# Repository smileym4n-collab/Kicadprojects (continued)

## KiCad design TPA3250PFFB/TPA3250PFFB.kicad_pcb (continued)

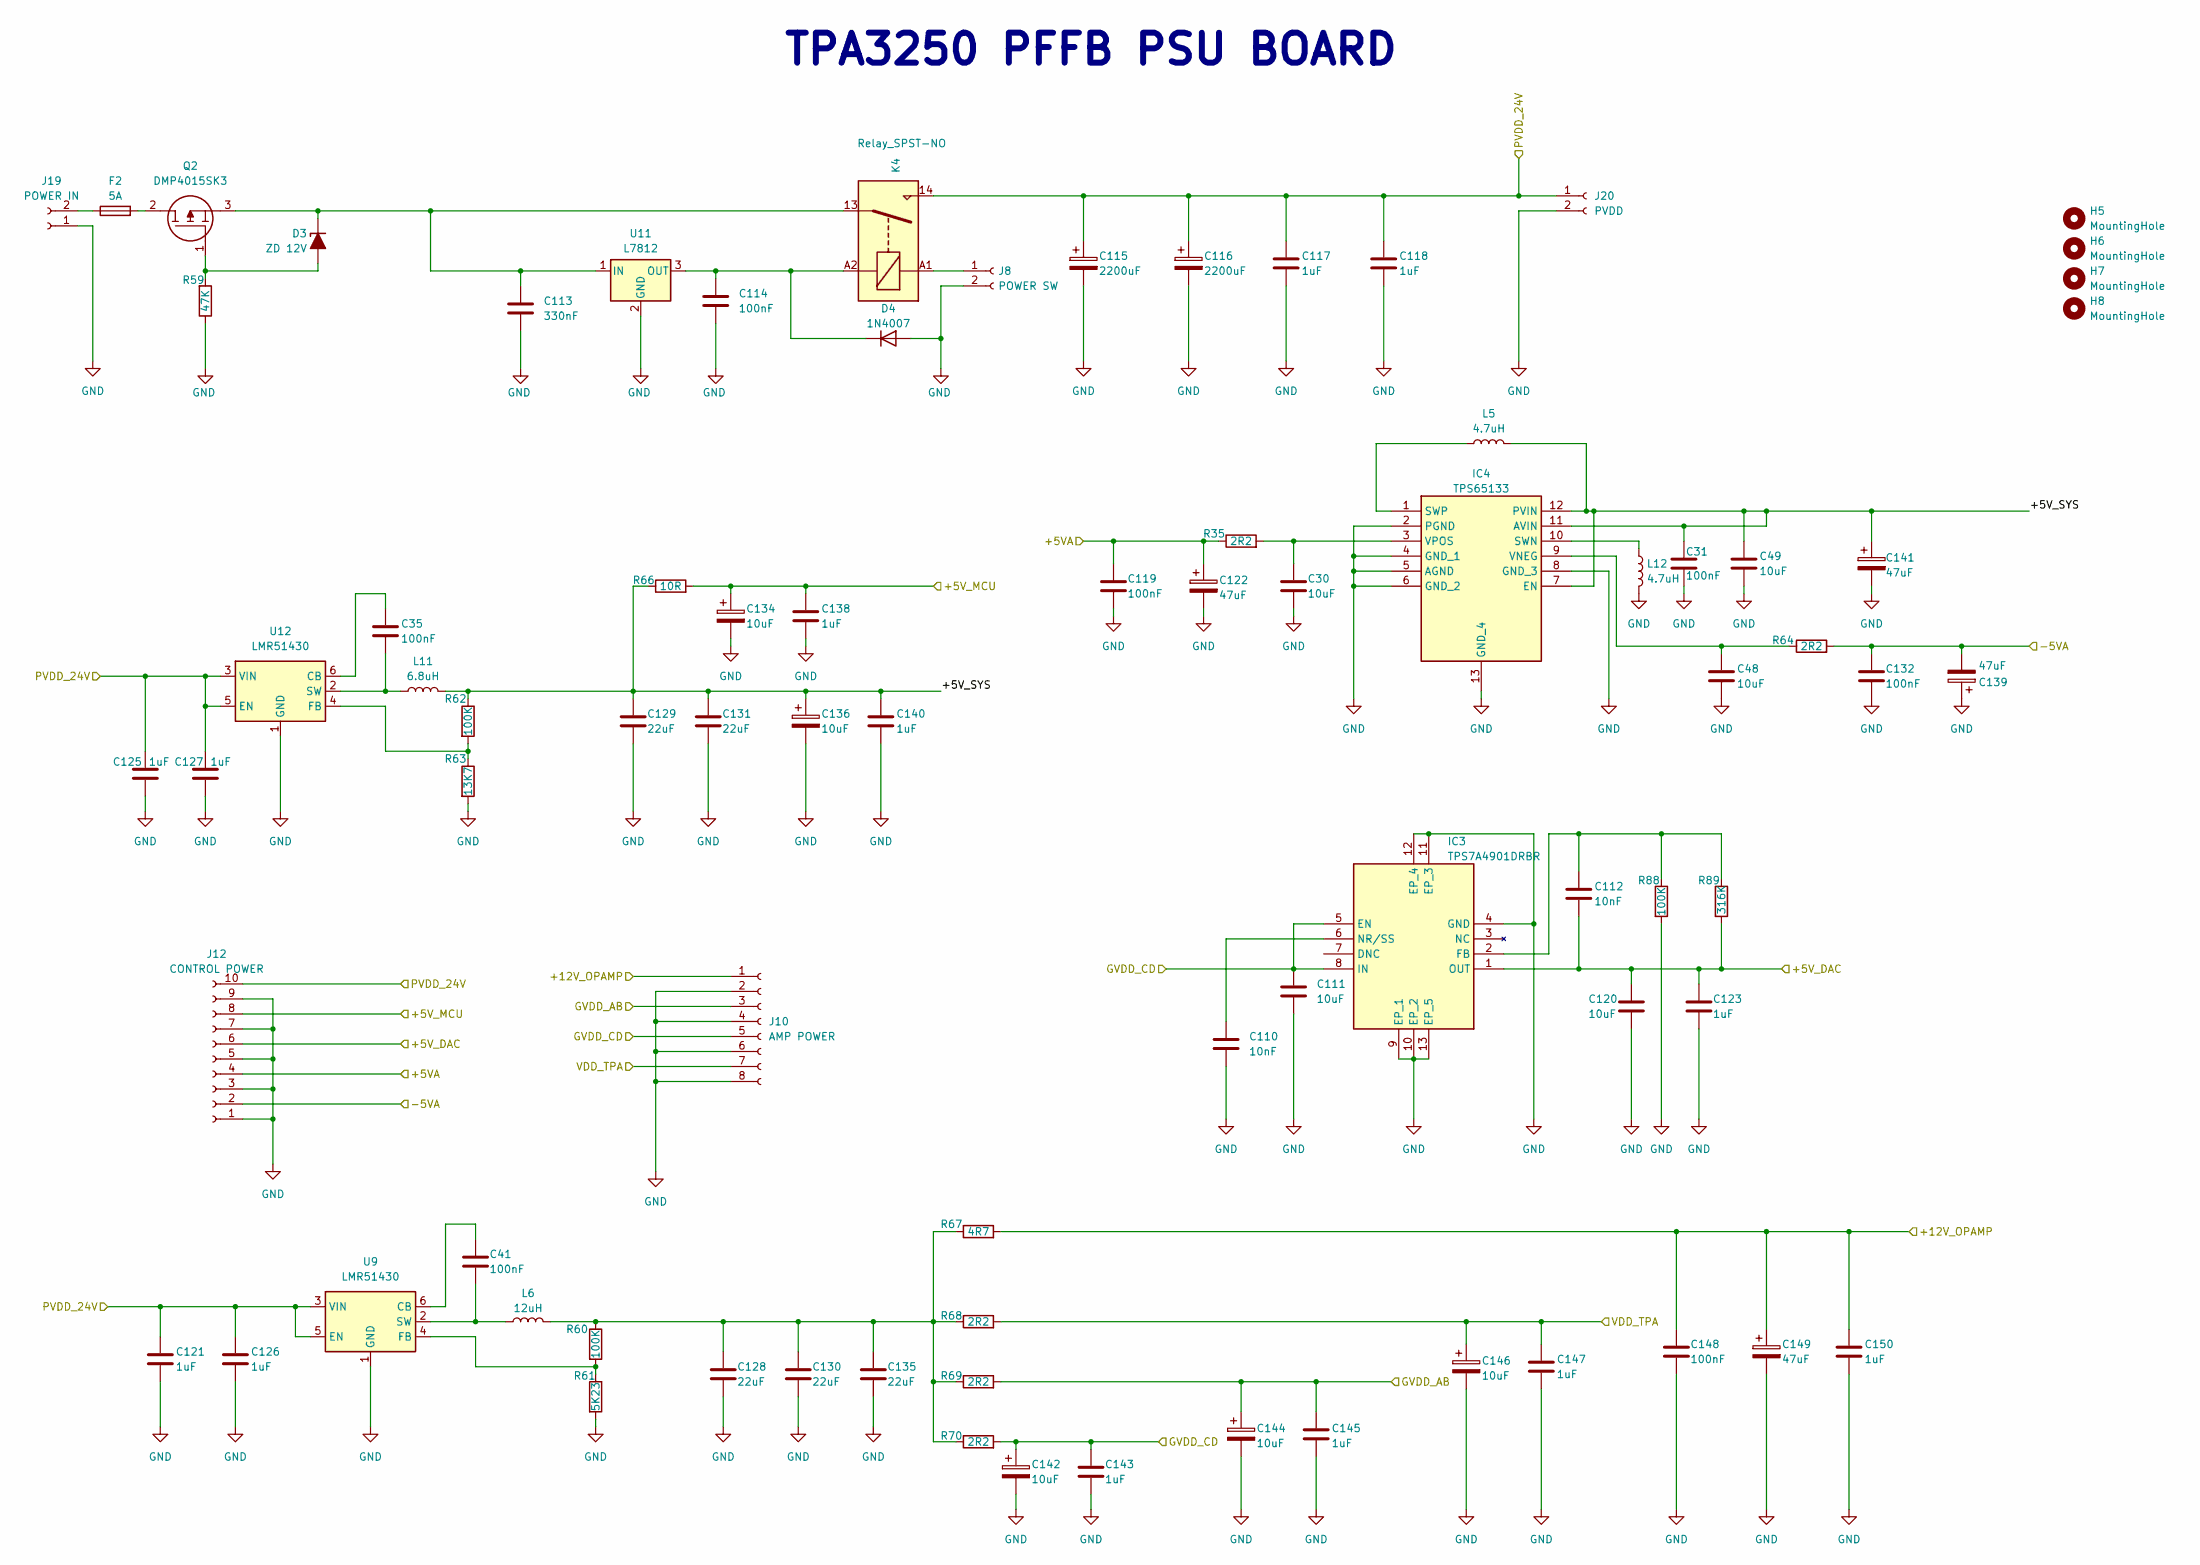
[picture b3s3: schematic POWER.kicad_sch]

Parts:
C30, C48, C49: 10uF; C_0805_2012Metric_Pad1.18x1.45mm_HandSolder
C31, C35, C41, C119, C132, C148: 100nF; C_1206_3216Metric_Pad1.33x1.80mm_HandSolder
C110, C112: 10nF; C_0805_2012Metric_Pad1.18x1.45mm_HandSolder
C111, C120: 10uF; C_1206_3216Metric_Pad1.33x1.80mm_HandSolder
C113: 330nF; C_Disc_D3.8mm_W2.6mm_P2.50mm
C114: 100nF; C_Disc_D3.8mm_W2.6mm_P2.50mm
C115, C116: 2200uF; CP_Radial_D16.0mm_P7.50mm
C117, C118, C121, C123, C125, C126, C127, C138, C140, C143, C145, C147, C150: 1uF; C_1206_3216Metric_Pad1.33x1.80mm_HandSolder
C122, C139, C141, C149: 47uF; CP_Radial_D5.0mm_P2.50mm
C128, C129, C130, C131, C135: 22uF; C_1206_3216Metric_Pad1.33x1.80mm_HandSolder
C134, C136, C142, C144, C146: 10uF; CP_Radial_D4.0mm_P2.00mm
D3: ZD 12V; D_DO-201AD_P12.70mm_Horizontal
D4: 1N4007; D_DO-41_SOD81_P10.16mm_Horizontal
F2: 5A; Fuse_Littelfuse_395Series
H5, H6, H7, H8: MountingHole; MountingHole_3.2mm_M3
IC3: TPS7A4901DRBR; Mouser Part Number 595-TPS7A4901DRBR
IC4: TPS65133; SON45P300X300X80-13N-D; Mouser Part Number 595-TPS65133DPDR
J8: POWER SW; JST_XH_B2B-XH-A_1x02_P2.50mm_Vertical
J10: AMP POWER; JST_XH_B8B-XH-A_1x08_P2.50mm_Vertical
J12: CONTROL POWER; JST_XH_B10B-XH-A_1x10_P2.50mm_Vertical
J19: POWER IN; Molex_KK-396_A-41791-0002_1x02_P3.96mm_Vertical
J20: PVDD; Molex_KK-396_A-41791-0002_1x02_P3.96mm_Vertical
K4: Relay_SPST-NO; Relay_SPST_TE_SDT-S-103LMR
L5, L12: 4.7uH; L_1008_2520Metric_Pad1.43x2.20mm_HandSolder
L6: 12uH; SRR1050A-120Y
L11: 6.8uH; SRP6030WA-6R8M
Q2: DMP4015SK3; DMP4015SK313; Manufacturer_Part_Number DMP4015SK3-13
R35, R64, R68, R69, R70: 2R2; R_0805_2012Metric_Pad1.20x1.40mm_HandSolder
R59: 47K; R_0805_2012Metric_Pad1.20x1.40mm_HandSolder
R60, R62, R88: 100K; R_0805_2012Metric_Pad1.20x1.40mm_HandSolder
R61: 5K23; R_0805_2012Metric_Pad1.20x1.40mm_HandSolder
R63: 13K7; R_0805_2012Metric_Pad1.20x1.40mm_HandSolder
R66: 10R; R_0805_2012Metric_Pad1.20x1.40mm_HandSolder
R67: 4R7; R_0805_2012Metric_Pad1.20x1.40mm_HandSolder
R89: 316K; R_0805_2012Metric_Pad1.20x1.40mm_HandSolder
U9, U12: LMR51430; SOT-23-6
U11: L7812; TO-220-3_Vertical

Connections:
/AMP/+12V_OPAMP: C148.1, C149.1, C150.1, J10.1, R67.2; also elsewhere on the board
/AMP/GVDD_AB: C144.1, C145.1, J10.3, R69.2; also elsewhere on the board
/AMP/GVDD_CD: C111.2, C142.1, C143.1, IC3.5 (EN), IC3.8 (IN), J10.5, R70.2; also elsewhere on the board
/AMP/PVDD_24V: C115.1, C116.1, C117.1, C118.1, C121.1, C125.1, C126.1, C127.1, J12.10, J20.1, K4.14, U9.3 (VIN), U9.5 (EN), U12.3 (VIN), U12.5 (EN); also elsewhere on the board
/AMP/VDD_TPA: C146.1, C147.1, J10.7, R68.2; also elsewhere on the board
/CONTROL/+5VA: C119.1, C122.1, J12.4, R35.1; also elsewhere on the board
/CONTROL/+5V_DAC: C112.2, C120.2, C123.2, IC3.1 (OUT), J12.6, R89.2; also elsewhere on the board
/CONTROL/+5V_MCU: C134.1, C138.1, J12.8, R66.2; also elsewhere on the board
/CONTROL/-5VA: C132.1, C139.2, J12.2, R64.2; also elsewhere on the board
/POWER/+5V_SYS: C31.1, C49.1, C129.1, C131.1, C136.1, C140.1, C141.1, IC4.7 (EN), IC4.11 (AVIN), IC4.12 (PVIN), L5.2, L11.2, R62.1, R66.1
GND: C30.2, C31.2, C48.2, C49.2, C110.2, C111.1, C113.2, C114.2, C115.2, C116.2, C117.2, C118.2, C119.2, C120.1, C121.2, C122.2, C123.1, C125.2, C126.2, C127.2, C128.2, C129.2, C130.2, C131.2, C132.2, C134.2, C135.2, C136.2, C138.2, C139.1, C140.2, C141.2, C142.2, C143.2, C144.2, C145.2, C146.2, C147.2, C148.2, C149.2, C150.2, D4.2 (A), IC3.4 (GND), IC3.9 (EP_1), IC3.10 (EP_2), IC3.11 (EP_3), IC3.12 (EP_4), IC3.13 (EP_5), IC4.2 (PGND), IC4.4 (GND_1), IC4.5 (AGND), IC4.6 (GND_2), IC4.8 (GND_3), IC4.13 (GND_4), J8.2, J10.2, J10.4, J10.6, J10.8, J12.1, J12.3, J12.5, J12.7, J12.9, J19.1, J20.2, L12.2, R59.1, R61.2, R63.2, R88.2, U9.1 (GND), U11.2 (GND), U12.1 (GND); also elsewhere on the board
unnamed: C128.1, C130.1, C135.1, L6.2, R60.1, R67.1, R68.1, R69.1, R70.1
unnamed: D3.2 (A), Q2.1, R59.2
unnamed: C113.1, D3.1 (K), K4.13, Q2.3, U11.1 (IN)
unnamed: C114.1, D4.1 (K), K4.A2, U11.3 (OUT)
unnamed: F2.2, Q2.2
unnamed: C112.1, IC3.2 (FB), R88.1, R89.1
unnamed: C110.1, IC3.6 (NR/SS)
unnamed: IC4.10 (SWN), L12.1
unnamed: IC4.1 (SWP), L5.1
unnamed: C48.1, IC4.9 (VNEG), R64.1
unnamed: C30.1, IC4.3 (VPOS), R35.2
unnamed: J8.1, K4.A1
unnamed: F2.1, J19.2
unnamed: C41.1, U9.6 (CB)
unnamed: R60.2, R61.1, U9.4 (FB)
unnamed: C41.2, L6.1, U9.2 (SW)
unnamed: C35.1, U12.6 (CB)
unnamed: R62.2, R63.1, U12.4 (FB)
unnamed: C35.2, L11.1, U12.2 (SW)

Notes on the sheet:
TPA3250 PFFB PSU BOARD

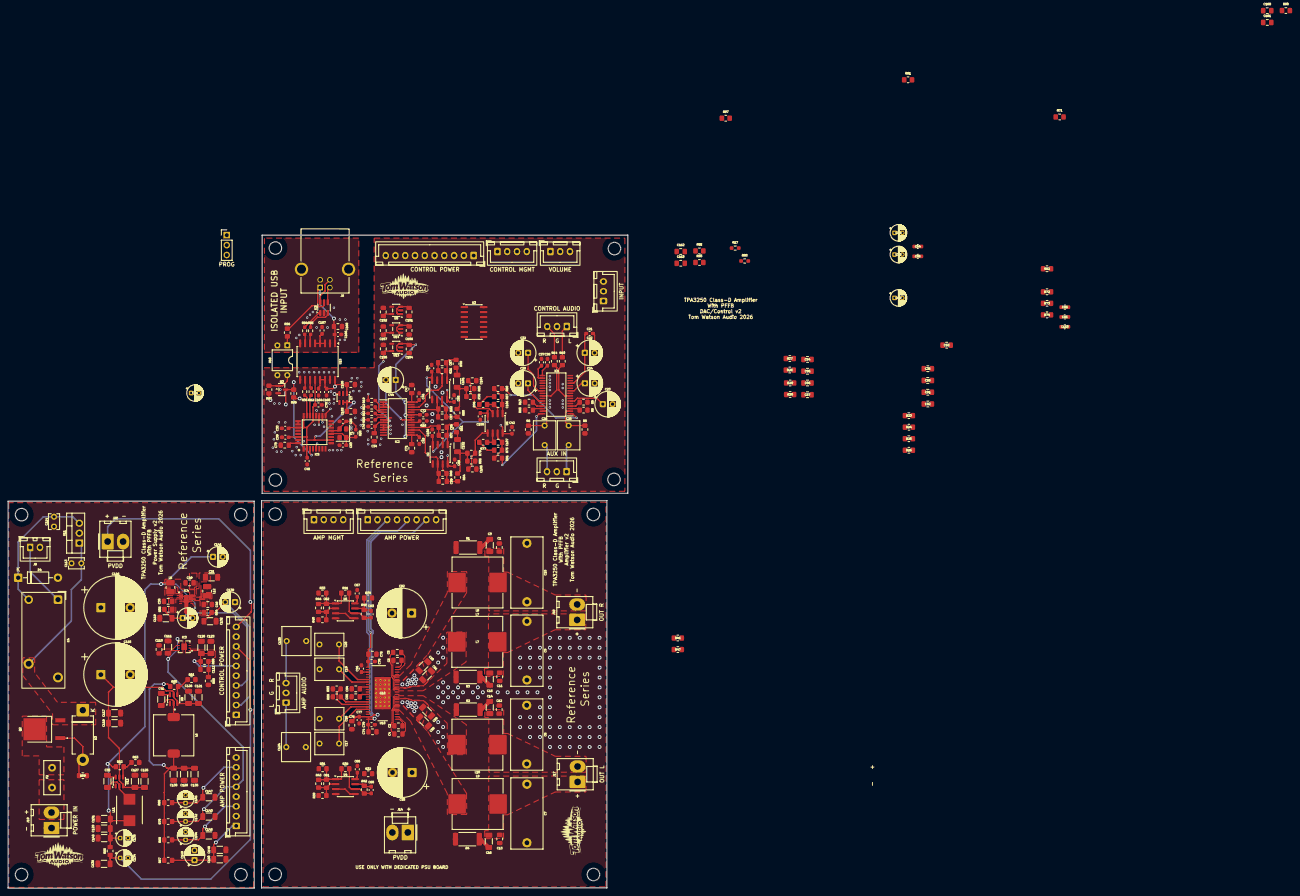
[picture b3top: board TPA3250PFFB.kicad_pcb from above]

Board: 4 copper layers, 158.6 x 167.0 mm, 324 parts (0 on the bottom side), 162 nets.

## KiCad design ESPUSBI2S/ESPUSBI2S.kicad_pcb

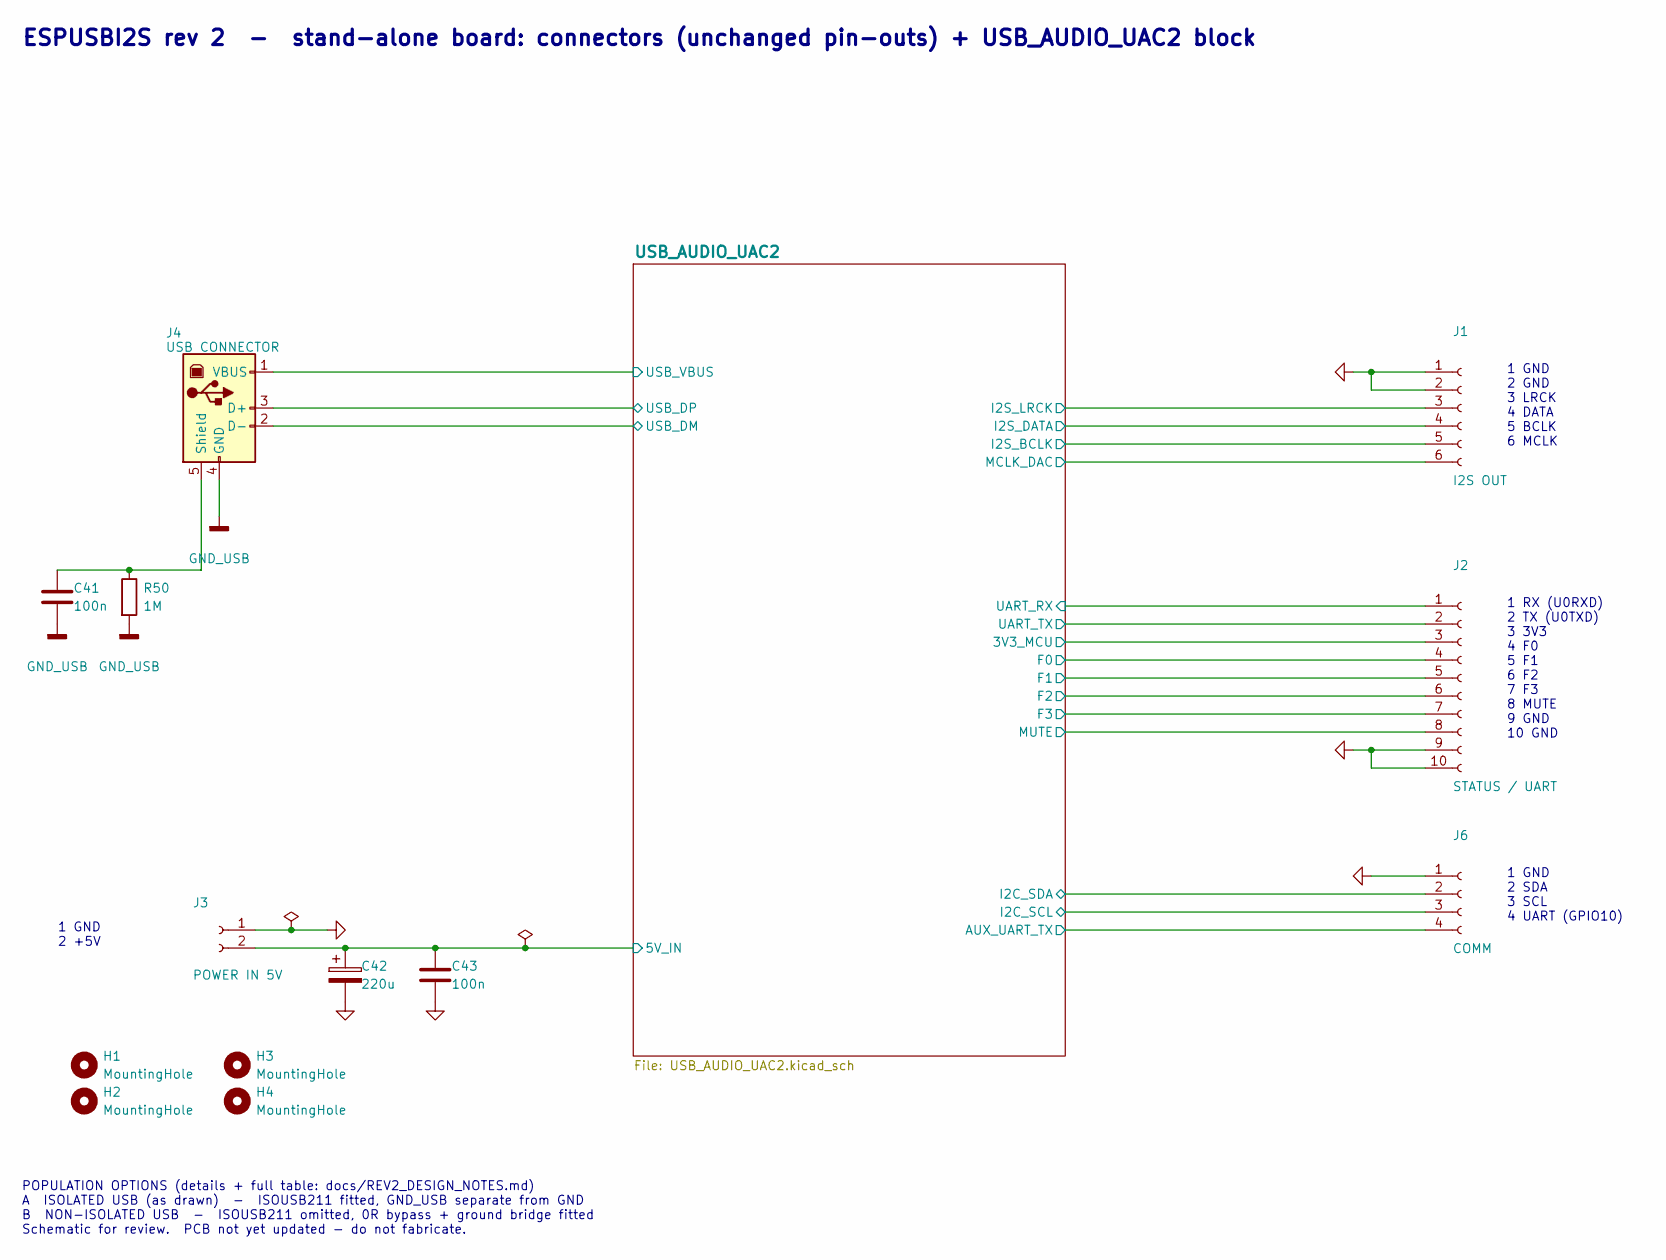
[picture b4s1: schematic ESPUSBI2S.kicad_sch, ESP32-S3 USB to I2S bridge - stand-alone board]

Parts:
C41, C43: 100n; C_0603_1608Metric; MPN MC0603B104K500CT
C42: 220u; CP_Radial_D6.3mm_P2.50mm; MPN EEUFR1C221B
H1, H2, H3, H4: MountingHole; MountingHole_3.2mm_M3
J1: I2S OUT; JST_XH_B6B-XH-A_1x06_P2.50mm_Vertical
J2: STATUS / UART; PinHeader_1x10_P2.54mm_Vertical
J3: POWER IN 5V; JST_XH_B2B-XH-A_1x02_P2.50mm_Vertical
J4: USB CONNECTOR; USBC
J6: COMM; PinHeader_1x04_P2.54mm_Vertical
R50: 1M; R_0603_1608Metric; MPN RC0603FR-101ML

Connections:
/USB_AUDIO_UAC2/3V3_MCU: J2.3; also elsewhere on the board
/USB_AUDIO_UAC2/5V_IN: C42.1, C43.1, J3.2; also elsewhere on the board
/USB_AUDIO_UAC2/AUX_UART_TX: J6.4; also elsewhere on the board
/USB_AUDIO_UAC2/F0: J2.4; also elsewhere on the board
/USB_AUDIO_UAC2/F1: J2.5; also elsewhere on the board
/USB_AUDIO_UAC2/F2: J2.6; also elsewhere on the board
/USB_AUDIO_UAC2/F3: J2.7; also elsewhere on the board
/USB_AUDIO_UAC2/I2C_SCL: J6.3; also elsewhere on the board
/USB_AUDIO_UAC2/I2C_SDA: J6.2; also elsewhere on the board
/USB_AUDIO_UAC2/I2S_BCLK: J1.5; also elsewhere on the board
/USB_AUDIO_UAC2/I2S_DATA: J1.4; also elsewhere on the board
/USB_AUDIO_UAC2/I2S_LRCK: J1.3; also elsewhere on the board
/USB_AUDIO_UAC2/MCLK_DAC: J1.6; also elsewhere on the board
/USB_AUDIO_UAC2/MUTE: J2.8; also elsewhere on the board
/USB_AUDIO_UAC2/UART_RX: J2.1; also elsewhere on the board
/USB_AUDIO_UAC2/UART_TX: J2.2; also elsewhere on the board
/USB_AUDIO_UAC2/USB_DM: J4.2 (D-); also elsewhere on the board
/USB_AUDIO_UAC2/USB_DP: J4.3 (D+); also elsewhere on the board
/USB_AUDIO_UAC2/USB_INTERFACE/USB_VBUS: J4.1 (VBUS); also elsewhere on the board
GND: C42.2, C43.2, J1.1, J1.2, J2.9, J2.10, J3.1, J6.1; also elsewhere on the board
GND_USB: C41.2, J4.4 (GND), R50.2; also elsewhere on the board
unnamed: C41.1, J4.5 (Shield), R50.1

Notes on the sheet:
POPULATION OPTIONS (details + full table: docs/REV2_DESIGN_NOTES.md) A ISOLATED USB (as drawn) - ISOUSB211 fitted, GND_USB separate from GND B NON-ISOLATED USB - ISOUSB211 omitted, 0R bypass + ground bridge fitted Schematic for review. PCB not yet updated - do not fabricate.
1 GND 2 SDA 3 SCL 4 UART (GPIO10)
ESPUSBI2S rev 2 - stand-alone board: connectors (unchanged pin-outs) + USB_AUDIO_UAC2 block
1 RX (U0RXD) 2 TX (U0TXD) 3 3V3 4 F0 5 F1 6 F2 7 F3 8 MUTE 9 GND 10 GND
1 GND 2 GND 3 LRCK 4 DATA 5 BCLK 6 MCLK
1 GND 2 +5V

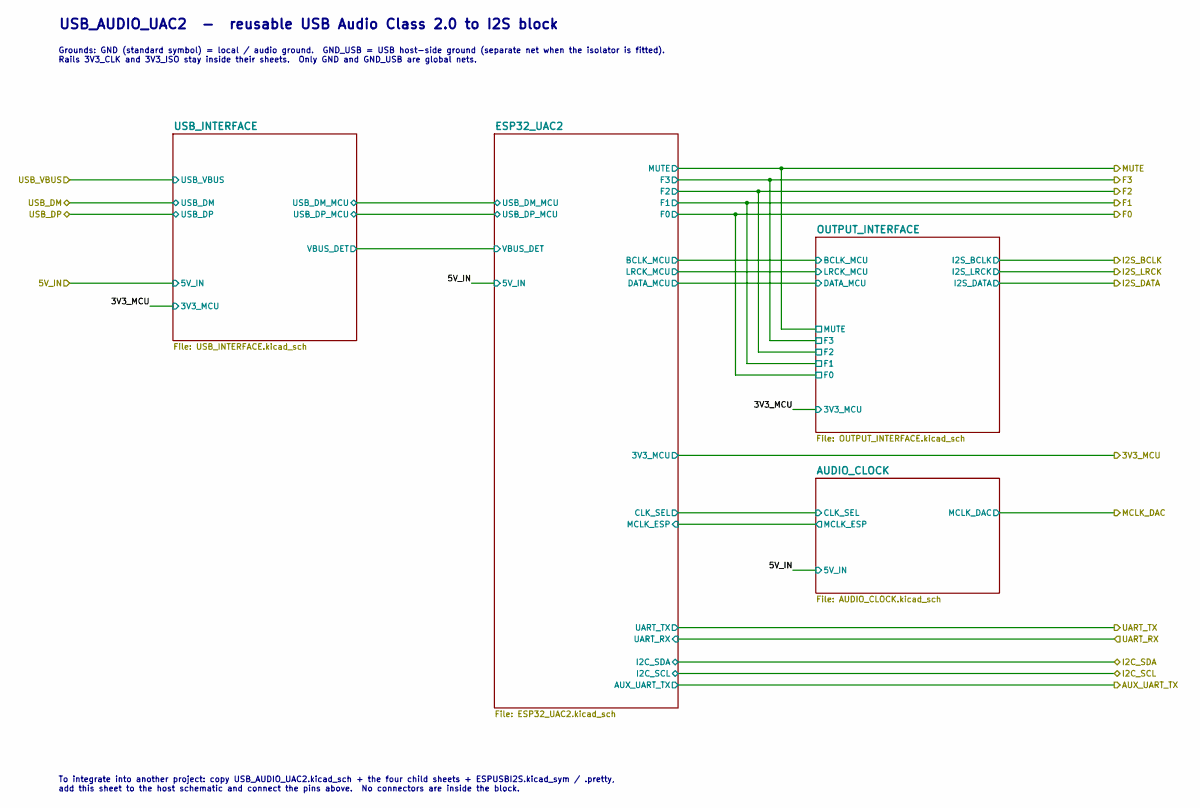
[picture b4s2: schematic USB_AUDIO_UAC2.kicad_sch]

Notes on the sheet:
Grounds: GND (standard symbol) = local / audio ground. GND_USB = USB host-side ground (separate net when the isolator is fitted). Rails 3V3_CLK and 3V3_ISO stay inside their sheets. Only GND and GND_USB are global nets.
To integrate into another project: copy USB_AUDIO_UAC2.kicad_sch + the four child sheets + ESPUSBI2S.kicad_sym / .pretty, add this sheet to the host schematic and connect the pins above. No connectors are inside the block.
USB_AUDIO_UAC2 - reusable USB Audio Class 2.0 to I2S block

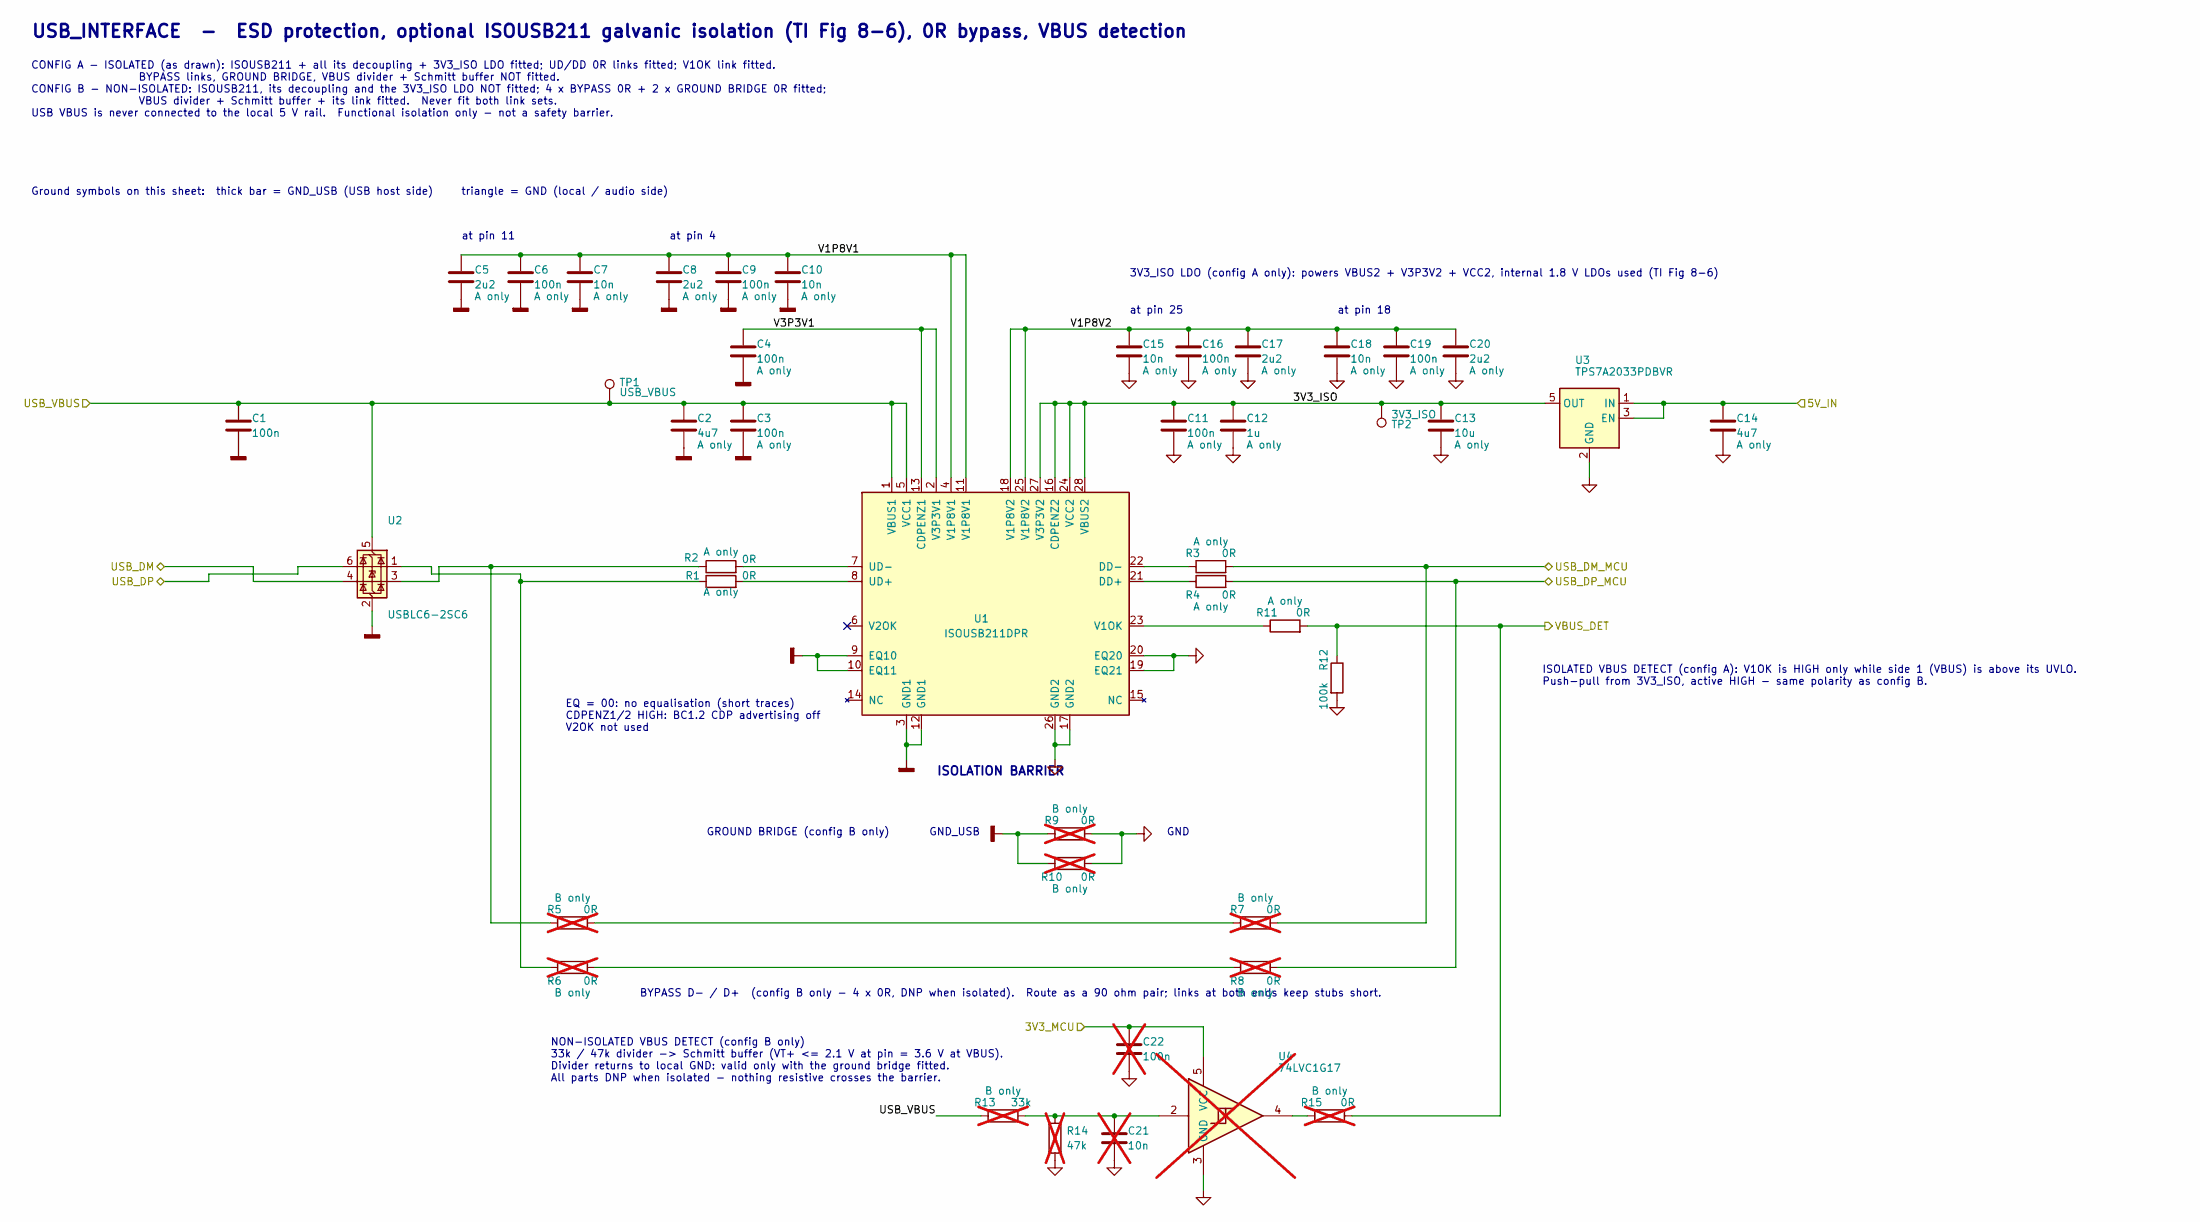
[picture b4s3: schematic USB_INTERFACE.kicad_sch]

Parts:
C1, C3, C4, C6, C9, C11, C16, C19: 100n; C_0603_1608Metric; MPN MC0603B104K500CT
C2, C14: 4u7; C_0805_2012Metric; MPN CL21A475KAQNNNE
C5, C8, C17, C20: 2u2; C_0805_2012Metric; MPN CL21B225KPFNNNE
C7, C10, C15, C18: 10n; C_0805_2012Metric; MPN 0805B103K500CT
C12: 1u; C_0805_2012Metric; MPN C0805C105K3RACTU
C13: 10u; C_1206_3216Metric; MPN TMK316B7106KL-TD
C21: 10n; C_0805_2012Metric; MPN 0805B103K500CT; not fitted
C22: 100n; C_0603_1608Metric; MPN MC0603B104K500CT; not fitted
R1, R2, R3, R4, R11: 0R; R_0805_2012Metric; MPN RK73Z2ATTD
R5, R6, R7, R8, R15: 0R; R_0805_2012Metric; MPN RK73Z2ATTD; not fitted
R9, R10: 0R; R_1206_3216Metric_Pad1.30x1.75mm_HandSolder; MPN RK73Z2ATTD; not fitted
R12: 100k; R_0805_2012Metric; MPN RK73B2ATTE104J
R13: 33k; R_0805_2012Metric; MPN MCWR08X3302FTL; not fitted
R14: 47k; R_0805_2012Metric; MPN RMCF0805FT47K0; not fitted
TP1: USB_VBUS; TestPoint_Pad_D1.0mm
TP2: 3V3_ISO; TestPoint_Pad_D1.0mm
U1: ISOUSB211DPR; ISOUSB211_DP0028A_SSOP-28_7.5x10.3mm_P0.65mm; MPN ISOUSB211DPR
U2: USBLC6-2SC6; SOT-23-6; MPN USBLC6-2SC6
U3: TPS7A2033PDBVR; SOT-23-5; MPN TPS7A2033PDBVR
U4: 74LVC1G17; SOT-23-5; MPN SN74LVC1G17DBVR; not fitted

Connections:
/USB_AUDIO_UAC2/3V3_MCU: C22.1, U4.5 (VCC); also elsewhere on the board
/USB_AUDIO_UAC2/5V_IN: C14.1, U3.1 (IN), U3.3 (EN); also elsewhere on the board
/USB_AUDIO_UAC2/ESP32_UAC2/USB_DM_MCU: R3.2, R7.2; also elsewhere on the board
/USB_AUDIO_UAC2/ESP32_UAC2/USB_DP_MCU: R4.2, R8.2; also elsewhere on the board
/USB_AUDIO_UAC2/ESP32_UAC2/VBUS_DET: R11.2, R12.1, R15.2; also elsewhere on the board
/USB_AUDIO_UAC2/USB_DM: U2.4 (I/O2); also elsewhere on the board
/USB_AUDIO_UAC2/USB_DP: U2.6 (I/O1); also elsewhere on the board
/USB_AUDIO_UAC2/USB_INTERFACE/3V3_ISO: C11.1, C12.1, C13.1, TP2.1 (1_1), U1.16 (CDPENZ2), U1.24 (VCC2), U1.27 (V3P3V2), U1.28 (VBUS2), U3.5 (OUT)
/USB_AUDIO_UAC2/USB_INTERFACE/USB_VBUS: C1.1, C2.1, C3.1, R13.1, TP1.1 (1_1), U1.1 (VBUS1), U1.5 (VCC1), U2.5 (VBUS); also elsewhere on the board
/USB_AUDIO_UAC2/USB_INTERFACE/V1P8V1: C5.1, C6.1, C7.1, C8.1, C9.1, C10.1, U1.4 (V1P8V1), U1.11 (V1P8V1)
/USB_AUDIO_UAC2/USB_INTERFACE/V1P8V2: C15.1, C16.1, C17.1, C18.1, C19.1, C20.1, U1.18 (V1P8V2), U1.25 (V1P8V2)
/USB_AUDIO_UAC2/USB_INTERFACE/V3P3V1: C4.1, U1.2 (V3P3V1), U1.13 (CDPENZ1)
GND: C11.2, C12.2, C13.2, C14.2, C15.2, C16.2, C17.2, C18.2, C19.2, C20.2, C21.2, C22.2, R9.2, R10.2, R12.2, R14.2, U1.17 (GND2), U1.19 (EQ21), U1.20 (EQ20), U1.26 (GND2), U3.2 (GND), U4.3 (GND); also elsewhere on the board
GND_USB: C1.2, C2.2, C3.2, C4.2, C5.2, C6.2, C7.2, C8.2, C9.2, C10.2, R9.1, R10.1, U1.3 (GND1), U1.9 (EQ10), U1.10 (EQ11), U1.12 (GND1), U2.2 (GND); also elsewhere on the board
unnamed: C21.1, R13.2, R14.1, U4.2
unnamed: R1.1, R6.1, U2.1 (I/O1)
unnamed: R2.1, R5.1, U2.3 (I/O2)
unnamed: R5.2, R7.1
unnamed: R6.2, R8.1
unnamed: R15.1, U4.4
unnamed: R4.1, U1.21 (DD+)
unnamed: R3.1, U1.22 (DD-)
unnamed: R1.2, U1.8 (UD+)
unnamed: R2.2, U1.7 (UD-)
unnamed: R11.1, U1.23 (V1OK)

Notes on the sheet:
at pin 25
EQ = 00: no equalisation (short traces) CDPENZ1/2 HIGH: BC1.2 CDP advertising off V2OK not used
GND_USB
ISOLATED VBUS DETECT (config A): V1OK is HIGH only while side 1 (VBUS) is above its UVLO. Push-pull from 3V3_ISO, active HIGH - same polarity as config B.
CONFIG A - ISOLATED (as drawn): ISOUSB211 + all its decoupling + 3V3_ISO LDO fitted; UD/DD 0R links fitted; V1OK link fitted. BYPASS links, GROUND BRIDGE, VBUS divider + Schmitt buffer NOT fitted. CONFIG B - NON-ISOLATED: ISOUSB211, its decoupling and the 3V3_ISO LDO NOT fitted; 4 x BYPASS 0R + 2 x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
Ground symbols on this sheet: thick bar = GND_USB (USB host side) triangle = GND (local / audio side)
GROUND BRIDGE (config B only)
NON-ISOLATED VBUS DETECT (config B only) 33k / 47k divider -> Schmitt buffer (VT+ <= 2.1 V at pin = 3.6 V at VBUS). Divider returns to local GND: valid only with the ground bridge fitted. All parts DNP when isolated - nothing resistive crosses the barrier.
GND
at pin 11
at pin 4
3V3_ISO LDO (config A only): powers VBUS2 + V3P3V2 + VCC2, internal 1.8 V LDOs used (TI Fig 8-6)
USB_INTERFACE - ESD protection, optional ISOUSB211 galvanic isolation (TI Fig 8-6), 0R bypass, VBUS detection
at pin 18
BYPASS D- / D+ (config B only - 4 x 0R, DNP when isolated). Route as a 90 ohm pair; links at both ends keep stubs short.
ISOLATION BARRIER

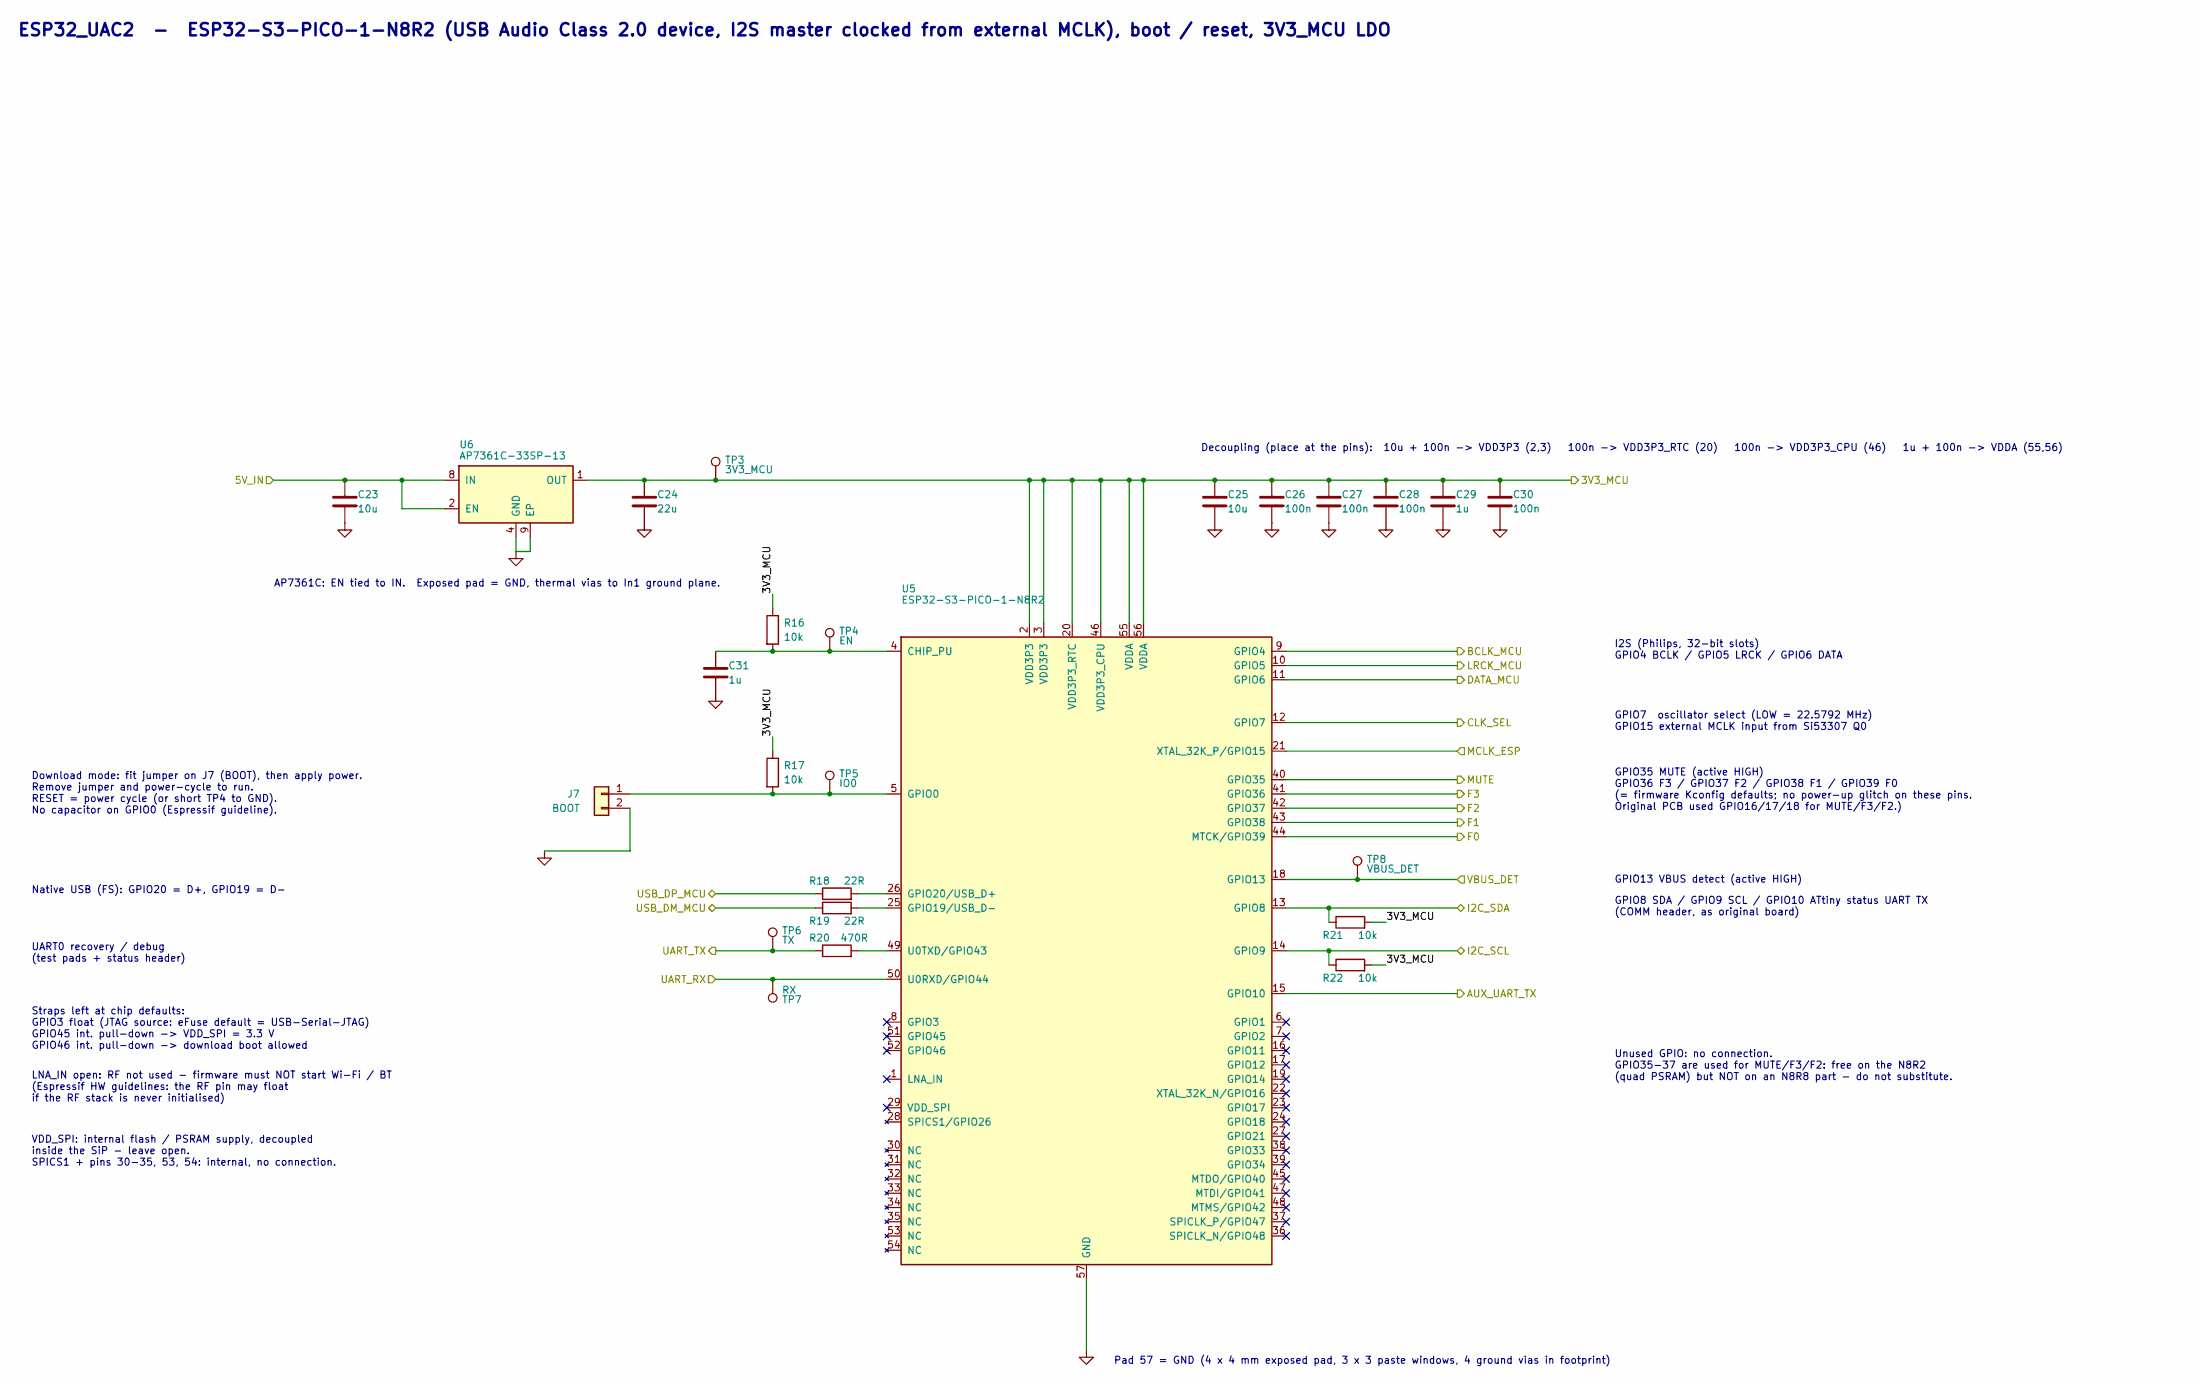
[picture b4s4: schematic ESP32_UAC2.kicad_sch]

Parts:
C23, C25: 10u; C_1206_3216Metric; MPN TMK316B7106KL-TD
C24: 22u; C_1206_3216Metric; MPN EMK316BB7226ML-T
C26, C27, C28, C30: 100n; C_0603_1608Metric; MPN MC0603B104K500CT
C29, C31: 1u; C_0805_2012Metric; MPN C0805C105K3RACTU
J7: BOOT; PinHeader_1x02_P2.54mm_Vertical
R16, R17, R21, R22: 10k; R_0603_1608Metric; MPN RC0603FR-0710KL
R18, R19: 22R; R_0603_1608Metric; MPN RK73B1JTTD220J
R20: 470R; R_0805_2012Metric; MPN ASC0805-470RFT5
TP3: 3V3_MCU; TestPoint_Pad_D1.0mm
TP4: EN; TestPoint_Pad_D1.0mm
TP5: IO0; TestPoint_Pad_D1.0mm
TP6: TX; TestPoint_Pad_D1.0mm
TP7: RX; TestPoint_Pad_D1.0mm
TP8: VBUS_DET; TestPoint_Pad_D1.0mm
U5: ESP32-S3-PICO-1-N8R2; ESP32-S3-PICO-1_LGA-56-1EP_7x7mm_P0.4mm; MPN ESP32-S3-PICO-1-N8R2
U6: AP7361C-33SP-13; Diodes_SO-8EP; MPN AP7361C-33SP-13

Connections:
/USB_AUDIO_UAC2/3V3_MCU: C24.1, C25.1, C26.1, C27.1, C28.1, C29.1, C30.1, R16.1, R17.1, R21.2, R22.2, TP3.1 (1_1), U5.2 (VDD3P3), U5.3 (VDD3P3), U5.20 (VDD3P3_RTC), U5.46 (VDD3P3_CPU), U5.55 (VDDA), U5.56 (VDDA), U6.1 (OUT); also elsewhere on the board
/USB_AUDIO_UAC2/5V_IN: C23.1, U6.2 (EN), U6.8 (IN); also elsewhere on the board
/USB_AUDIO_UAC2/AUDIO_CLOCK/CLK_SEL: U5.12 (GPIO7); also elsewhere on the board
/USB_AUDIO_UAC2/AUDIO_CLOCK/MCLK_ESP: U5.21 (XTAL_32K_P/GPIO15); also elsewhere on the board
/USB_AUDIO_UAC2/AUX_UART_TX: U5.15 (GPIO10); also elsewhere on the board
/USB_AUDIO_UAC2/ESP32_UAC2/BCLK_MCU: U5.9 (GPIO4); also elsewhere on the board
/USB_AUDIO_UAC2/ESP32_UAC2/DATA_MCU: U5.11 (GPIO6); also elsewhere on the board
/USB_AUDIO_UAC2/ESP32_UAC2/LRCK_MCU: U5.10 (GPIO5); also elsewhere on the board
/USB_AUDIO_UAC2/ESP32_UAC2/USB_DM_MCU: R19.1; also elsewhere on the board
/USB_AUDIO_UAC2/ESP32_UAC2/USB_DP_MCU: R18.1; also elsewhere on the board
/USB_AUDIO_UAC2/ESP32_UAC2/VBUS_DET: TP8.1 (1_1), U5.18 (GPIO13); also elsewhere on the board
/USB_AUDIO_UAC2/F0: U5.44 (MTCK/GPIO39); also elsewhere on the board
/USB_AUDIO_UAC2/F1: U5.43 (GPIO38); also elsewhere on the board
/USB_AUDIO_UAC2/F2: U5.42 (GPIO37); also elsewhere on the board
/USB_AUDIO_UAC2/F3: U5.41 (GPIO36); also elsewhere on the board
/USB_AUDIO_UAC2/I2C_SCL: R22.1, U5.14 (GPIO9); also elsewhere on the board
/USB_AUDIO_UAC2/I2C_SDA: R21.1, U5.13 (GPIO8); also elsewhere on the board
/USB_AUDIO_UAC2/MUTE: U5.40 (GPIO35); also elsewhere on the board
/USB_AUDIO_UAC2/UART_RX: TP7.1 (1_1), U5.50 (U0RXD/GPIO44); also elsewhere on the board
/USB_AUDIO_UAC2/UART_TX: R20.1, TP6.1 (1_1); also elsewhere on the board
GND: C23.2, C24.2, C25.2, C26.2, C27.2, C28.2, C29.2, C30.2, C31.2, J7.2, U5.57 (GND), U6.4 (GND), U6.9 (EP); also elsewhere on the board
unnamed: J7.1, R17.2, TP5.1 (1_1), U5.5 (GPIO0)
unnamed: C31.1, R16.2, TP4.1 (1_1), U5.4 (CHIP_PU)
unnamed: R19.2, U5.25 (GPIO19/USB_D-)
unnamed: R18.2, U5.26 (GPIO20/USB_D+)
unnamed: R20.2, U5.49 (U0TXD/GPIO43)

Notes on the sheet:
UART0 recovery / debug (test pads + status header)
Native USB (FS): GPIO20 = D+, GPIO19 = D-
Decoupling (place at the pins): 10u + 100n -> VDD3P3 (2,3) 100n -> VDD3P3_RTC (20) 100n -> VDD3P3_CPU (46) 1u + 100n -> VDDA (55,56)
GPIO8 SDA / GPIO9 SCL / GPIO10 ATtiny status UART TX (COMM header, as original board)
ESP32_UAC2 - ESP32-S3-PICO-1-N8R2 (USB Audio Class 2.0 device, I2S master clocked from external MCLK), boot / reset, 3V3_MCU LDO
AP7361C: EN tied to IN. Exposed pad = GND, thermal vias to In1 ground plane.
VDD_SPI: internal flash / PSRAM supply, decoupled inside the SiP - leave open. SPICS1 + pins 30-35, 53, 54: internal, no connection.
Straps left at chip defaults: GPIO3 float (JTAG source: eFuse default = USB-Serial-JTAG) GPIO45 int. pull-down -> VDD_SPI = 3.3 V GPIO46 int. pull-down -> download boot allowed
I2S (Philips, 32-bit slots) GPIO4 BCLK / GPIO5 LRCK / GPIO6 DATA
GPIO35 MUTE (active HIGH) GPIO36 F3 / GPIO37 F2 / GPIO38 F1 / GPIO39 F0 (= firmware Kconfig defaults; no power-up glitch on these pins. Original PCB used GPIO16/17/18 for MUTE/F3/F2.)
GPIO13 VBUS detect (active HIGH)
Download mode: fit jumper on J7 (BOOT), then apply power. Remove jumper and power-cycle to run. RESET = power cycle (or short TP4 to GND). No capacitor on GPIO0 (Espressif guideline).
LNA_IN open: RF not used - firmware must NOT start Wi-Fi / BT (Espressif HW guidelines: the RF pin may float if the RF stack is never initialised)
Unused GPIO: no connection. GPIO35-37 are used for MUTE/F3/F2: free on the N8R2 (quad PSRAM) but NOT on an N8R8 part - do not substitute.
Pad 57 = GND (4 x 4 mm exposed pad, 3 x 3 paste windows, 4 ground vias in footprint)
GPIO7 oscillator select (LOW = 22.5792 MHz) GPIO15 external MCLK input from Si53307 Q0
